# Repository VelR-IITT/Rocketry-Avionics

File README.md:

# Rocketry-Avionics 🚀

Welcome to the **Rocketry-Avionics** repository! This project is dedicated to the development of avionics systems for rocketry. It contains all the necessary files, code, and documentation to help you understand, build, and contribute to the project. 
---
## 📁 Repository Contents

This repository contains the following:

### 1. **Images** 📷
Contains visual assets, diagrams, and photos related to the project. These images are useful for understanding the design and assembly of components.

### 2. **Files for Components** 📄
Includes schematics, datasheets, and design files for various components used in the avionics system. These files are essential for replicating or modifying the project.

### 3. **Code** 💻
Contains the source code for the avionics system. This includes firmware, scripts, and any software required to operate the rocket's electronics.

### 4. **Instructions** 📝
Step-by-step guides and documentation to help you set up, assemble, and troubleshoot the avionics system.

---

## 📧 Contact

🌐 GitHub: [Pratham Chintamani](https://github.com/prathamchintamani) \
🌐 GitHub: [Pratik Raj](https://github.com/0823pratik)\
🌐 GitHub: [Bhavesh Jain](https://github.com/Bhavesh-Ja1n)\
🌐 GitHub: [Sravan Gantla](https://github.com/sravangantla007)

---

Happy building! 🚀✨

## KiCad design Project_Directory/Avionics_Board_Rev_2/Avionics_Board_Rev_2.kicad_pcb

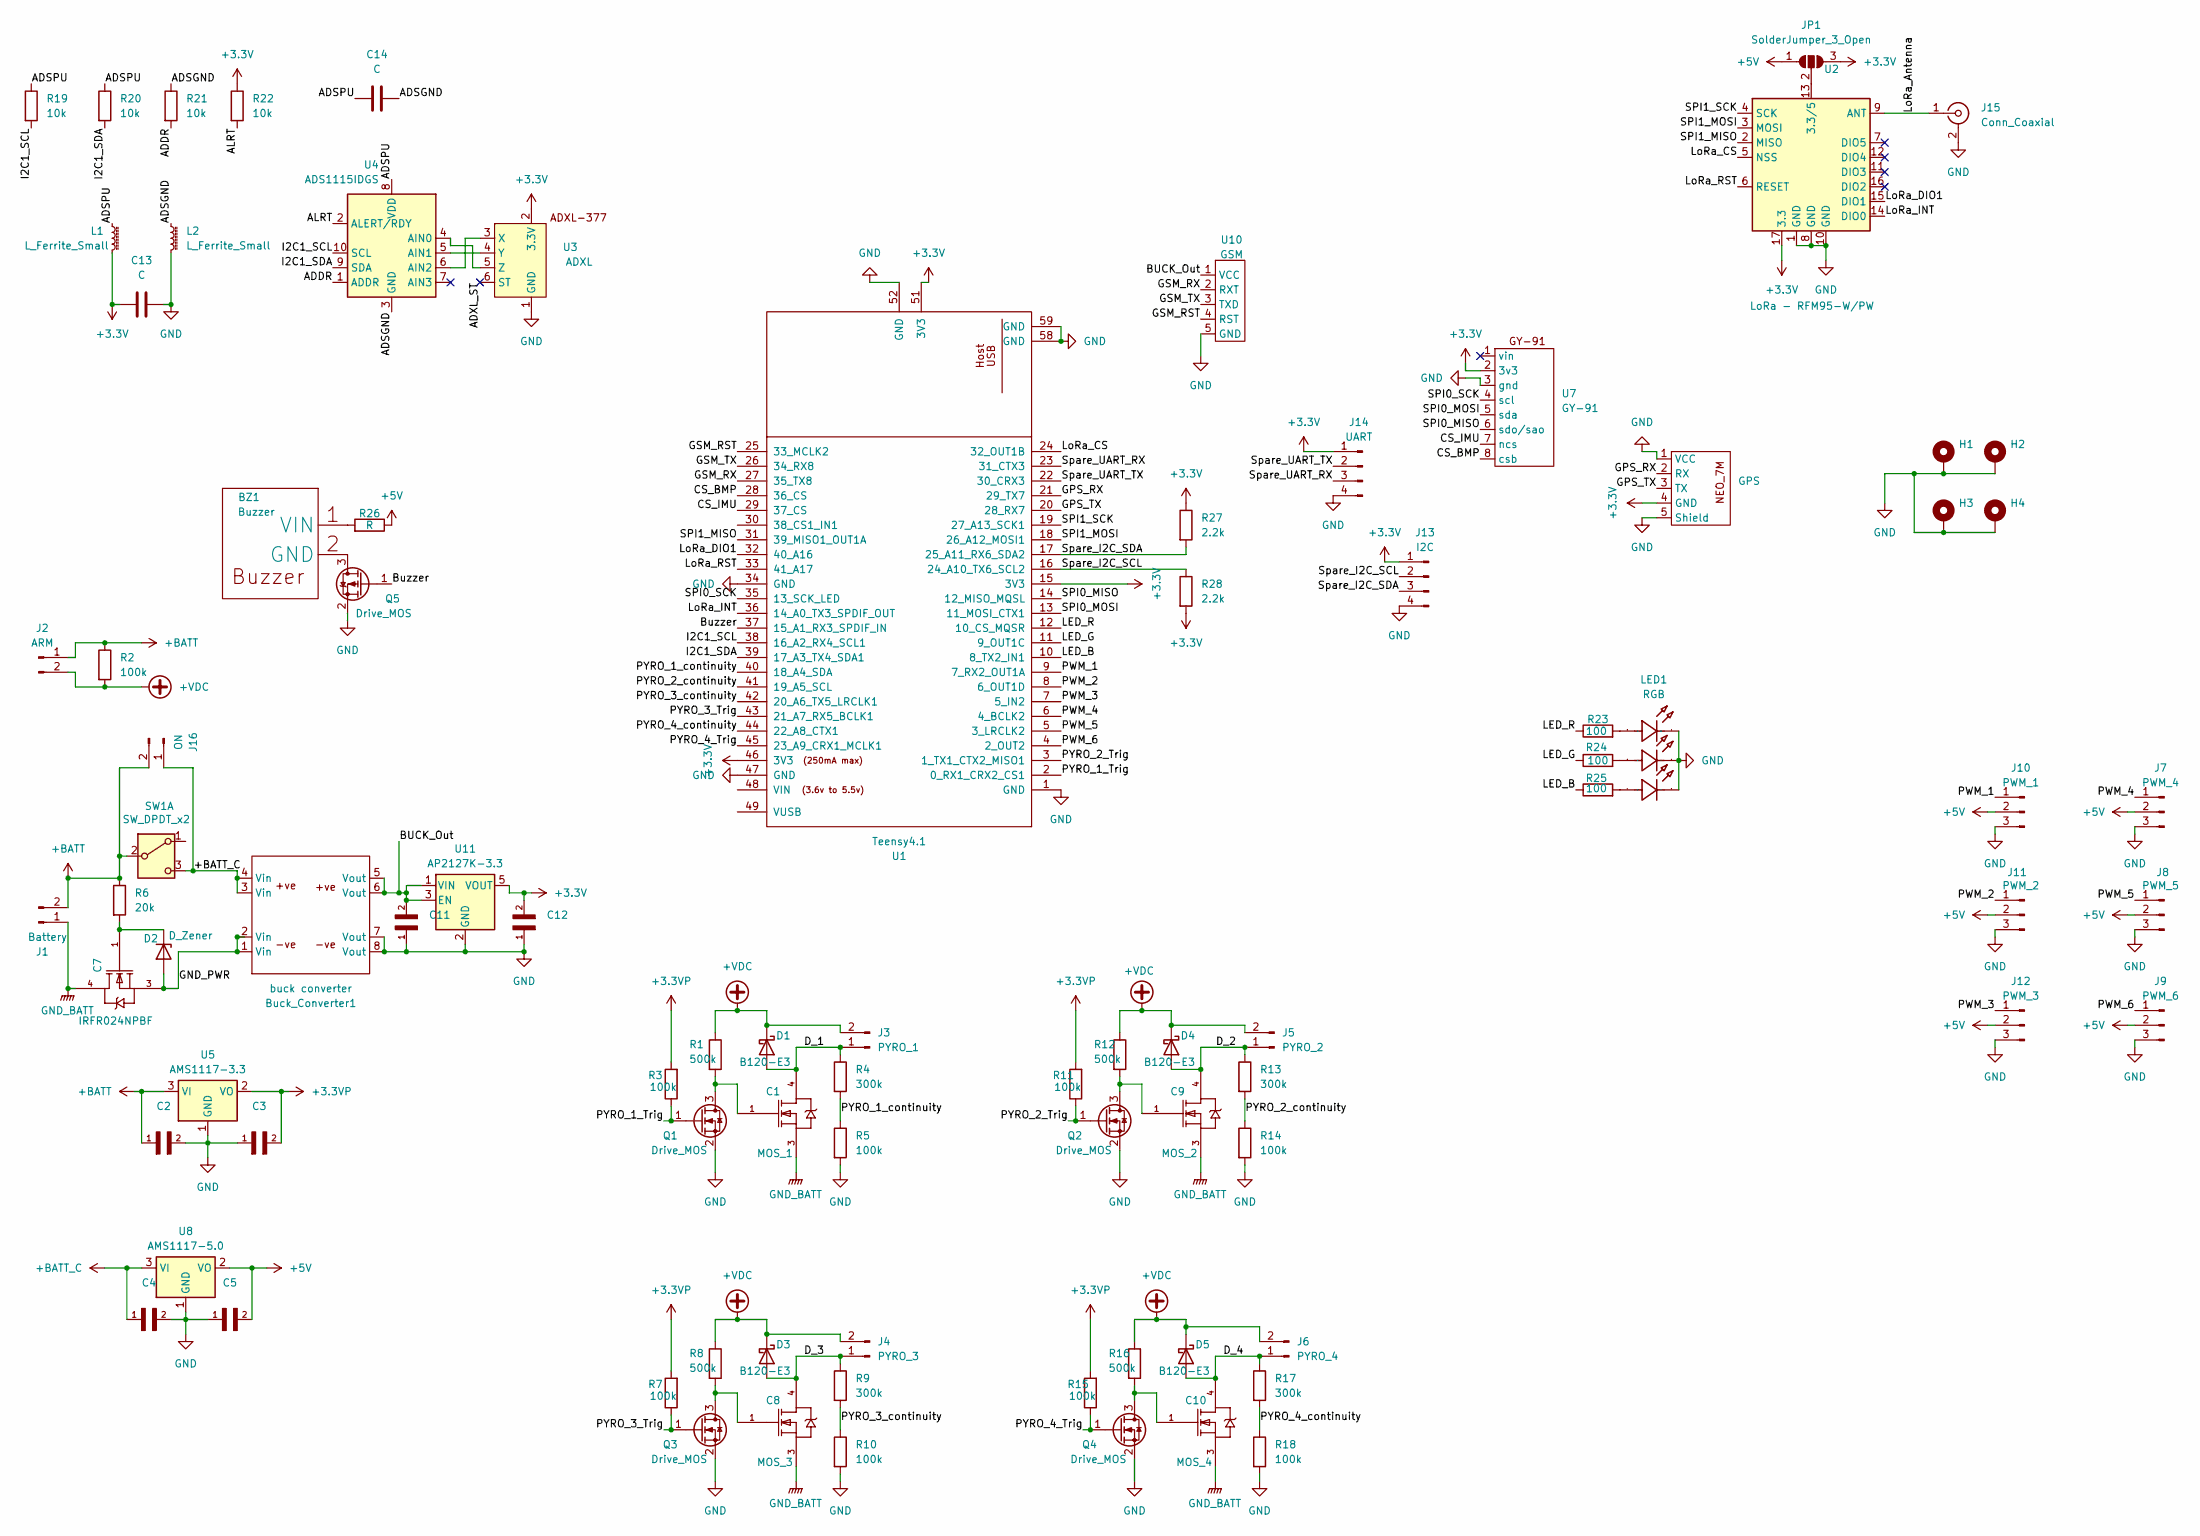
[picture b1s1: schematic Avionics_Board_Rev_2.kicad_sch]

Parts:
BZ1: Buzzer; Buzzer_TMB12A05
Buck_Converter1: buck converter; buck converter_corrected
C1: MOS_1; IRFR024NTRPBF-HXY Mosfet
C2, C3, C4, C5, C11, C12: C_0603_1608Metric_Pad1.08x0.95mm_HandSolder
C7: IRFR024NPBF; IRFR024NTRPBF-HXY Mosfet
C8: MOS_3; IRFR024NTRPBF-HXY Mosfet
C9: MOS_2; IRFR024NTRPBF-HXY Mosfet
C10: MOS_4; IRFR024NTRPBF-HXY Mosfet
C13: C; C_1206_3216Metric_Pad1.33x1.80mm_HandSolder
C14: C; C_1210_3225Metric_Pad1.33x2.70mm_HandSolder
D1, D3, D4, D5: B120-E3; D_SMA
D2: D_Zener; diode_
H1, H2, H3, H4: MountingHole_Pad; MountingHole_3.2mm_M3_DIN965_Pad_TopBottom
J1: Battery; AMASS_XT60PW-M_1x02_P7.20mm_Horizontal
J2: ARM; TerminalBlock_Phoenix_MKDS-1,5-2-5.08_1x02_P5.08mm_Horizont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
J3: PYRO_1; TerminalBlock_Phoenix_MKDS-1,5-2_1x02_P5.00mm_Horizontal
J4: PYRO_3; TerminalBlock_Phoenix_MKDS-1,5-2_1x02_P5.00mm_Horizontal
J5: PYRO_2; TerminalBlock_Phoenix_MKDS-1,5-2_1x02_P5.00mm_Horizontal
J6: PYRO_4; TerminalBlock_Phoenix_MKDS-1,5-2_1x02_P5.00mm_Horizontal
J7: PWM_4; PinHeader_1x03_P2.54mm_Vertical
J8: PWM_5; PinHeader_1x03_P2.54mm_Vertical
J9: PWM_6; PinHeader_1x03_P2.54mm_Vertical
J10: PWM_1; PinHeader_1x03_P2.54mm_Vertical
J11: PWM_2; PinHeader_1x03_P2.54mm_Vertical
J12: PWM_3; PinHeader_1x03_P2.54mm_Vertical
J13: I2C; JST_EH_B4B-EH-A_1x04_P2.50mm_Vertical
J14: UART; JST_EH_B4B-EH-A_1x04_P2.50mm_Vertical
J15: Conn_Coaxial; SMA_Samtec_SMA-J-P-H-ST-EM1_EdgeMount
J16: ON; TerminalBlock_Phoenix_MKDS-1,5-2-5.08_1x02_P5.08mm_Horizont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
JP1: SolderJumper_3_Open; SolderJumper-3_P2.0mm_Open_TrianglePad1.0x1.5mm
L1, L2: L_Ferrite_Small; L_1206_3216Metric_Pad1.22x1.90mm_HandSolder
LED1: RGB; XL-z3535rgbasg_RGB_LED; Manufacturer Part XL-Z3535RGBA-SG
Q1, Q2, Q3, Q4, Q5: Drive_MOS; SOT-23
R1, R8, R12, R16: 500k; R_1206_3216Metric_Pad1.30x1.75mm_HandSolder
R2, R3, R5, R7, R10, R11, R14, R15, R18: 100k; R_1206_3216Metric_Pad1.30x1.75mm_HandSolder
R4, R9, R13, R17: 300k; R_1206_3216Metric_Pad1.30x1.75mm_HandSolder
R6: 20k; R_1206_3216Metric_Pad1.30x1.75mm_HandSolder
R19, R20, R21, R22: 10k; C_1206_3216Metric_Pad1.33x1.80mm_HandSolder
R23, R24, R25: 100; R_1206_3216Metric_Pad1.30x1.75mm_HandSolder
R26: R; R_1206_3216Metric_Pad1.30x1.75mm_HandSolder
R27, R28: 2.2k; R_1206_3216Metric_Pad1.30x1.75mm_HandSolder
SW1: SW_DPDT_x2; Switch exp
U1: Teensy4.1; Teensy_4.1
U2: LoRa - RFM95-W/PW; RFM95W,PW
U3: ADXL; ADXL377_SparkFun_Module
U4: ADS1115IDGS; TSSOP-10_3x3mm_P0.5mm
U5: AMS1117-3.3; SOT-223-3_TabPin2
U6: GPS; JST-SH 1mm 4 Pin Male E Type Vertical Single Row WTB Connec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
U7: GY-91; gy91
U8: AMS1117-5.0; SOT-223-3_TabPin2
U10: GSM; JST_EH_B5B-EH-A_1x05_P2.50mm_Vertical
U11: AP2127K-3.3; SOT-23-5

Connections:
+3.3V: C12.2, C13.1, J13.1, J14.1, JP1.3 (B), L1.2, R22.1, R27.1, R28.2, U1.15 (3V3), U1.46 (3V3), U1.51 (3V3), U2.17 (3.3), U3.2 (3.3V), U6.4 (GND), U7.2 (3v3), U11.5 (VOUT)
+3.3VP: C3.2, R3.2, R7.2, R11.2, R15.2, U5.2 (VO)
+5V: C5.2, J7.2, J8.2, J9.2, J10.2, J11.2, J12.2, JP1.1 (A), R26.1, U8.2 (VO)
+BATT: C2.1, J1.2, J2.1, J16.2, R2.1, R6.1, SW1.2 (B), U5.3 (VI)
+BATT_C: Buck_Converter1.3 (Vin), Buck_Converter1.4 (Vin), C4.1, J16.1, SW1.3 (C), U8.3 (VI)
+VDC: D1.1 (K), D3.1 (K), D4.1 (K), D5.1 (K), J2.2, J3.2, J4.2, J5.2, J6.2, R1.1, R2.2, R8.1, R12.1, R16.1
/ADDR: R21.2, U4.1 (ADDR)
/ADSGND: C14.2, L2.1, R21.1, U4.3 (GND)
/ADSPU: C14.1, L1.1, R19.1, R20.1, U4.8 (VDD)
/ADXL_ST: U3.6 (ST)
/ALRT: R22.2, U4.2 (ALERT/RDY)
/BUCK_Out: Buck_Converter1.5 (Vout), Buck_Converter1.6 (Vout), C11.2, U10.1 (VCC), U11.1 (VIN), U11.3 (EN)
/Buzzer: Q5.1 (G), U1.37 (15_A1_RX3_SPDIF_IN)
/CS_BMP: U1.28 (36_CS), U7.8 (csb)
/CS_IMU: U1.29 (37_CS), U7.7 (ncs)
/D_1: C1.4, D1.2 (A), J3.1, R4.1
/D_2: C9.4, D4.2 (A), J5.1, R13.1
/D_3: C8.4, D3.2 (A), J4.1, R9.1
/D_4: C10.4, D5.2 (A), J6.1, R17.1
/GND_PWR: Buck_Converter1.1 (Vin), Buck_Converter1.2 (Vin), C7.3, D2.2 (A)
/GPS_RX: U1.21 (29_TX7), U6.2 (RX)
/GPS_TX: U1.20 (28_RX7), U6.3 (TX)
/GSM_RST: U1.25 (33_MCLK2), U10.4 (RST)
/GSM_RX: U1.27 (35_TX8), U10.2 (RXT)
/GSM_TX: U1.26 (34_RX8), U10.3 (TXD)
/I2C1_SCL: R19.2, U1.38 (16_A2_RX4_SCL1), U4.10 (SCL)
/I2C1_SDA: R20.2, U1.39 (17_A3_TX4_SDA1), U4.9 (SDA)
/LED_B: R25.1, U1.10 (8_TX2_IN1)
/LED_G: R24.1, U1.11 (9_OUT1C)
/LED_R: R23.1, U1.12 (10_CS_MQSR)
/LoRa_Antenna: J15.1 (In), U2.9 (ANT)
/LoRa_CS: U1.24 (32_OUT1B), U2.5 (NSS)
/LoRa_DIO1: U1.32 (40_A16), U2.15 (DIO1)
/LoRa_INT: U1.36 (14_A0_TX3_SPDIF_OUT), U2.14 (DIO0)
/LoRa_RST: U1.33 (41_A17), U2.6 (RESET)
/PWM_1: J10.1, U1.9 (7_RX2_OUT1A)
/PWM_2: J11.1, U1.8 (6_OUT1D)
/PWM_3: J12.1, U1.7 (5_IN2)
/PWM_4: J7.1, U1.6 (4_BCLK2)
/PWM_5: J8.1, U1.5 (3_LRCLK2)
/PWM_6: J9.1, U1.4 (2_OUT2)
/PYRO_1_Trig: Q1.1 (G), R3.1, U1.2 (0_RX1_CRX2_CS1)
/PYRO_1_continuity: R4.2, R5.1, U1.40 (18_A4_SDA)
/PYRO_2_Trig: Q2.1 (G), R11.1, U1.3 (1_TX1_CTX2_MISO1)
/PYRO_2_continuity: R13.2, R14.1, U1.41 (19_A5_SCL)
/PYRO_3_Trig: Q3.1 (G), R7.1, U1.43 (21_A7_RX5_BCLK1)
/PYRO_3_continuity: R9.2, R10.1, U1.42 (20_A6_TX5_LRCLK1)
/PYRO_4_Trig: Q4.1 (G), R15.1, U1.45 (23_A9_CRX1_MCLK1)
/PYRO_4_continuity: R17.2, R18.1, U1.44 (22_A8_CTX1)
/SPI0_MISO: U1.14 (12_MISO_MQSL), U7.6 (sdo/sao)
/SPI0_MOSI: U1.13 (11_MOSI_CTX1), U7.5 (sda)
/SPI0_SCK: U1.35 (13_SCK_LED), U7.4 (scl)
/SPI1_MISO: U1.31 (39_MISO1_OUT1A), U2.2 (MISO)
/SPI1_MOSI: U1.18 (26_A12_MOSI1), U2.3 (MOSI)
/SPI1_SCK: U1.19 (27_A13_SCK1), U2.4 (SCK)
/Spare_I2C_SCL: J13.2, R28.1, U1.16 (24_A10_TX6_SCL2)
/Spare_I2C_SDA: J13.3, R27.2, U1.17 (25_A11_RX6_SDA2)
/Spare_UART_RX: J14.3, U1.23 (31_CTX3)
/Spare_UART_TX: J14.2, U1.22 (30_CRX3)
GND: Buck_Converter1.7 (Vout), Buck_Converter1.8 (Vout), C2.2, C3.1, C4.2, C5.1, C11.1, C12.1, C13.2, H1.1, H2.1, H3.1, H4.1, J7.3, J8.3, J9.3, J10.3, J11.3, J12.3, J13.4, J14.4, J15.2 (Ext), L2.2, LED1.1 (-), LED1.2 (-), LED1.3 (1), Q1.2 (S), Q2.2 (S), Q3.2 (S), Q4.2 (S), Q5.2 (S), R5.2, R10.2, R14.2, R18.2, U1.1 (GND), U1.34 (GND), U1.47 (GND), U1.52 (GND), U1.58 (GND), U1.59 (GND), U2.1 (GND), U2.8 (GND), U2.10 (GND), U3.1 (GND), U5.1 (GND), U6.1 (VCC), U6.5 (Shield), U7.3 (gnd), U8.1 (GND), U10.5 (GND), U11.2 (GND)
GND_BATT: C1.3, C7.4, C8.3, C9.3, C10.3, J1.1
unnamed: BZ1.2 (GND), Q5.3 (D)
unnamed: BZ1.1 (VIN), R26.2
unnamed: C7.1, D2.1 (K), R6.2
unnamed: JP1.2 (C), U2.13 (3.3/5)
unnamed: LED1.4 (+), R23.2
unnamed: LED1.5 (+), R24.2
unnamed: LED1.6 (+), R25.2
unnamed: C1.1, Q1.3 (D), R1.2
unnamed: C9.1, Q2.3 (D), R12.2
unnamed: C8.1, Q3.3 (D), R8.2
unnamed: C10.1, Q4.3 (D), R16.2
unnamed: U3.3 (X), U4.6 (AIN2)
unnamed: U3.4 (Y), U4.5 (AIN1)
unnamed: U3.5 (Z), U4.4 (AIN0)

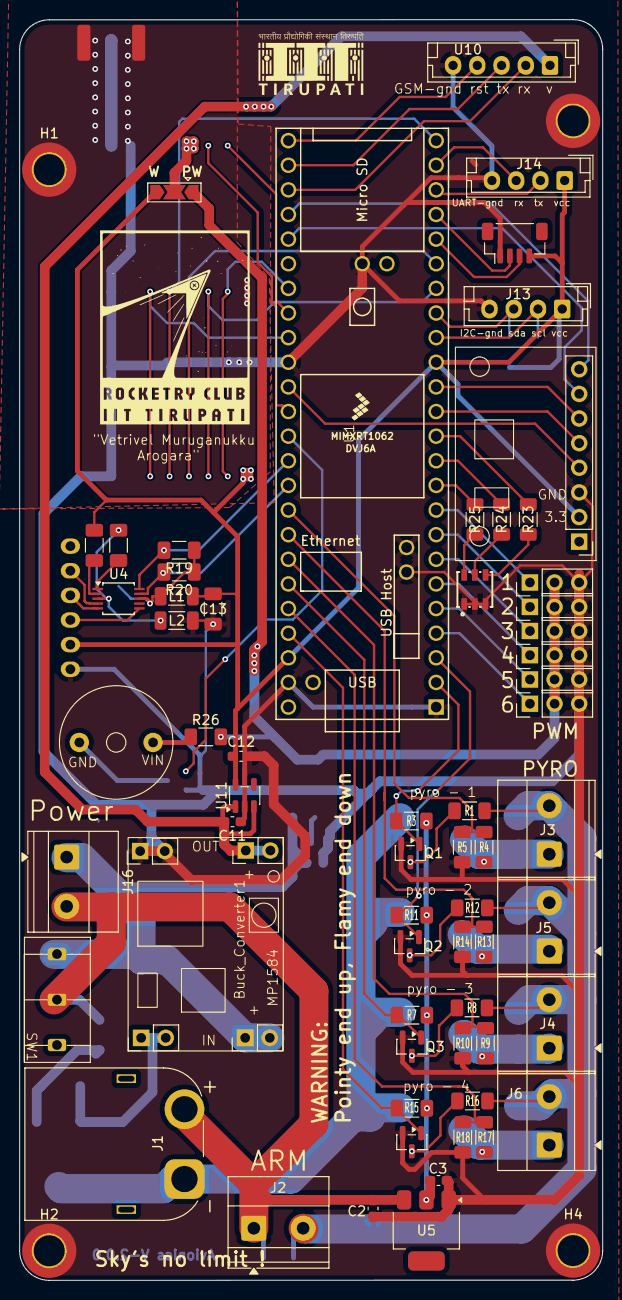
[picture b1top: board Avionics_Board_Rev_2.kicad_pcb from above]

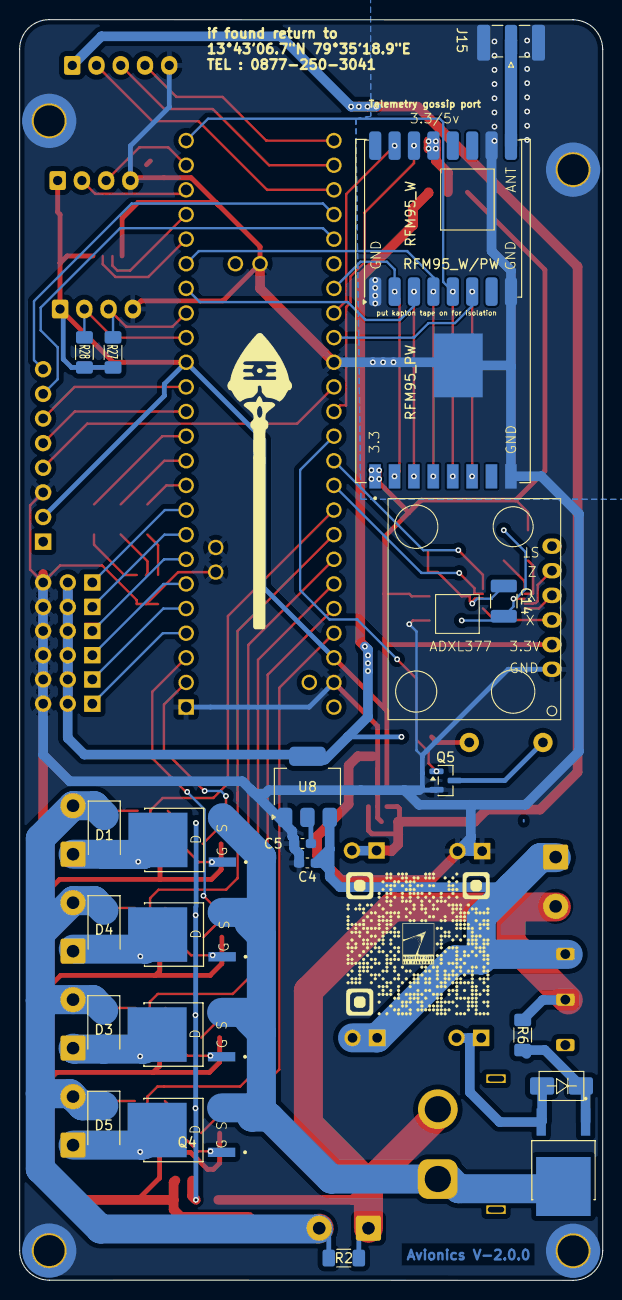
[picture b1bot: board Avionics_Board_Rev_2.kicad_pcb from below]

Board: 2 copper layers, 60.1 x 130.0 mm, 88 parts (22 on the bottom side), 74 nets.

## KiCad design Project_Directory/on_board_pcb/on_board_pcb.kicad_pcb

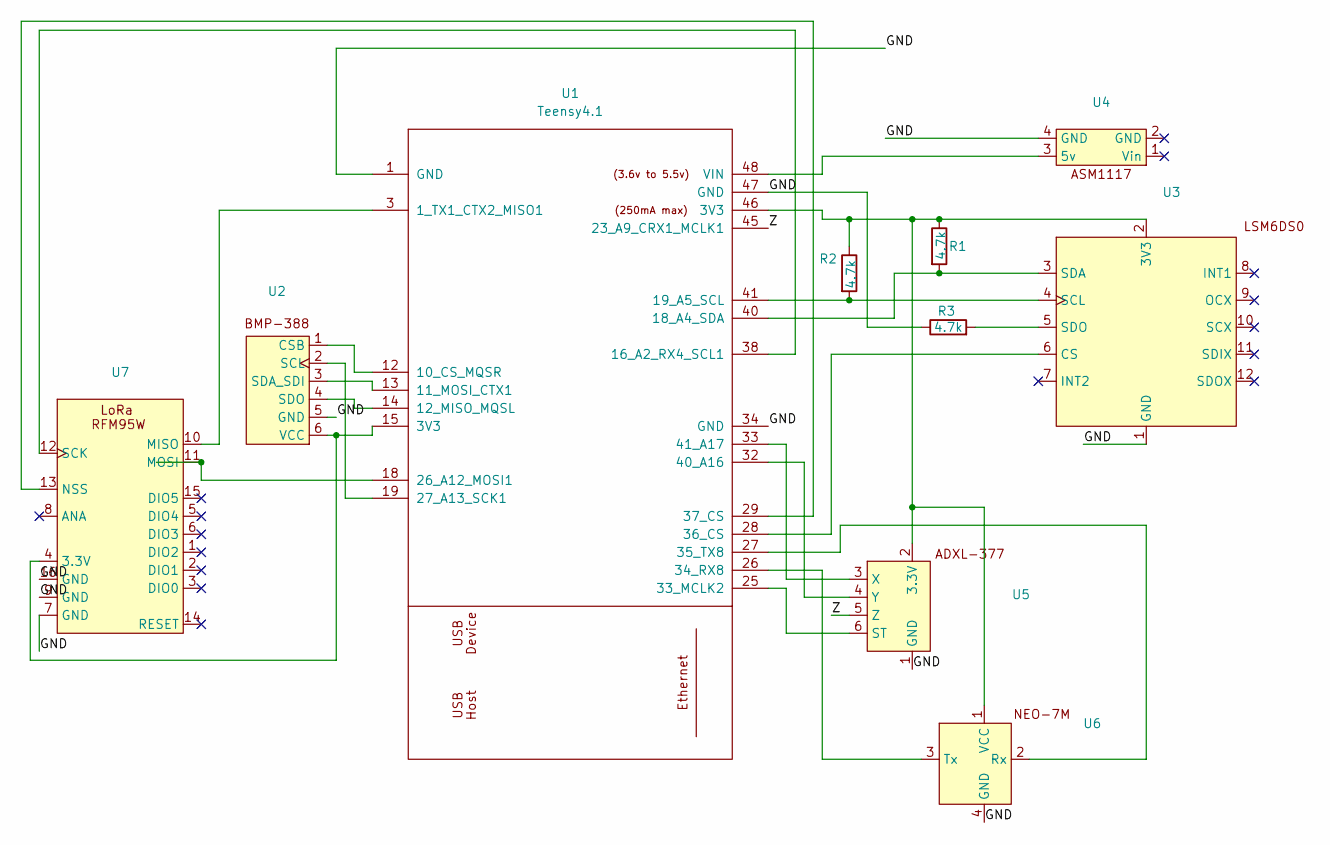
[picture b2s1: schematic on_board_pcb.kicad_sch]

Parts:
R1, R2, R3: 4.7k; R_Axial_DIN0207_L6.3mm_D2.5mm_P7.62mm_Horizontal
U1: Teensy4.1; Teensy-4.1
U2: BMP388
U3: LSM6DS0
U4: AMS1117
U5: ADXL377
U6: NEO_7M
U7: RFM95W

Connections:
/GND: R3.1, U1.1 (GND), U1.34 (GND), U1.47 (GND), U2.5 (GND), U3.1 (GND), U4.4 (GND), U5.1 (GND), U6.4 (GND), U7.7 (GND), U7.9 (GND), U7.16 (GND)
/Z: U1.45 (23_A9_CRX1_MCLK1), U5.5 (Z)
unnamed: U1.3 (1_TX1_CTX2_MISO1), U7.10 (MISO)
unnamed: U1.12 (10_CS_MQSR), U2.1 (CSB)
unnamed: U1.13 (11_MOSI_CTX1), U2.3 (SDA_SDI)
unnamed: U1.14 (12_MISO_MQSL), U2.4 (SDO)
unnamed: U1.38 (16_A2_RX4_SCL1), U7.12 (SCK)
unnamed: R1.2, U1.40 (18_A4_SDA), U3.3 (SDA)
unnamed: R2.2, U1.41 (19_A5_SCL), U3.4 (SCL)
unnamed: U1.18 (26_A12_MOSI1), U7.11 (MOSI)
unnamed: U1.19 (27_A13_SCK1), U2.2 (SCL)
unnamed: U1.25 (33_MCLK2), U5.6 (ST)
unnamed: U1.26 (34_RX8), U6.3 (Tx)
unnamed: U1.27 (35_TX8), U6.2 (Rx)
unnamed: U1.28 (36_CS), U3.6 (CS)
unnamed: U1.29 (37_CS), U7.13 (NSS)
unnamed: U1.32 (40_A16), U5.4 (Y)
unnamed: U1.33 (41_A17), U5.3 (X)
unnamed: U1.48 (VIN), U4.3 (5v)
unnamed: U1.15 (3V3), U2.6 (VCC), U7.4 (3.3V)
unnamed: R1.1, R2.1, U1.46 (3V3), U3.2 (3V3), U5.2 (3.3V), U6.1 (VCC)
unnamed: R3.2, U3.5 (SDO)

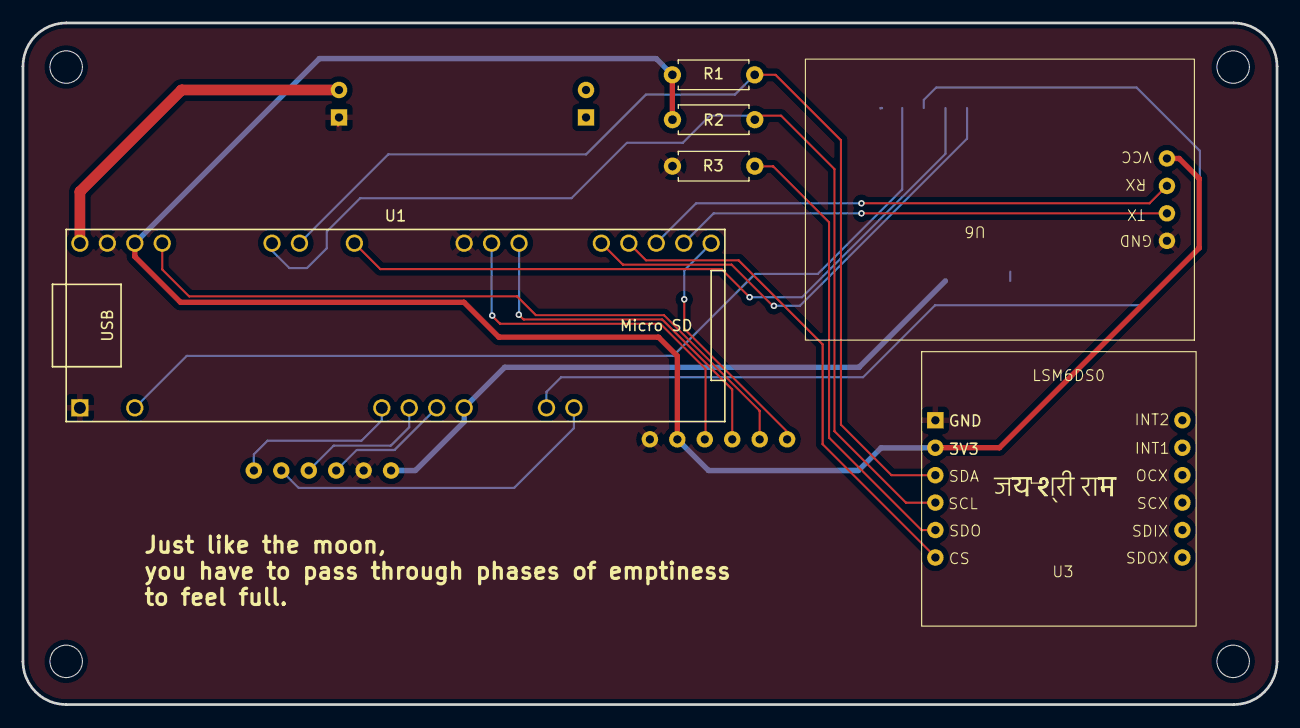
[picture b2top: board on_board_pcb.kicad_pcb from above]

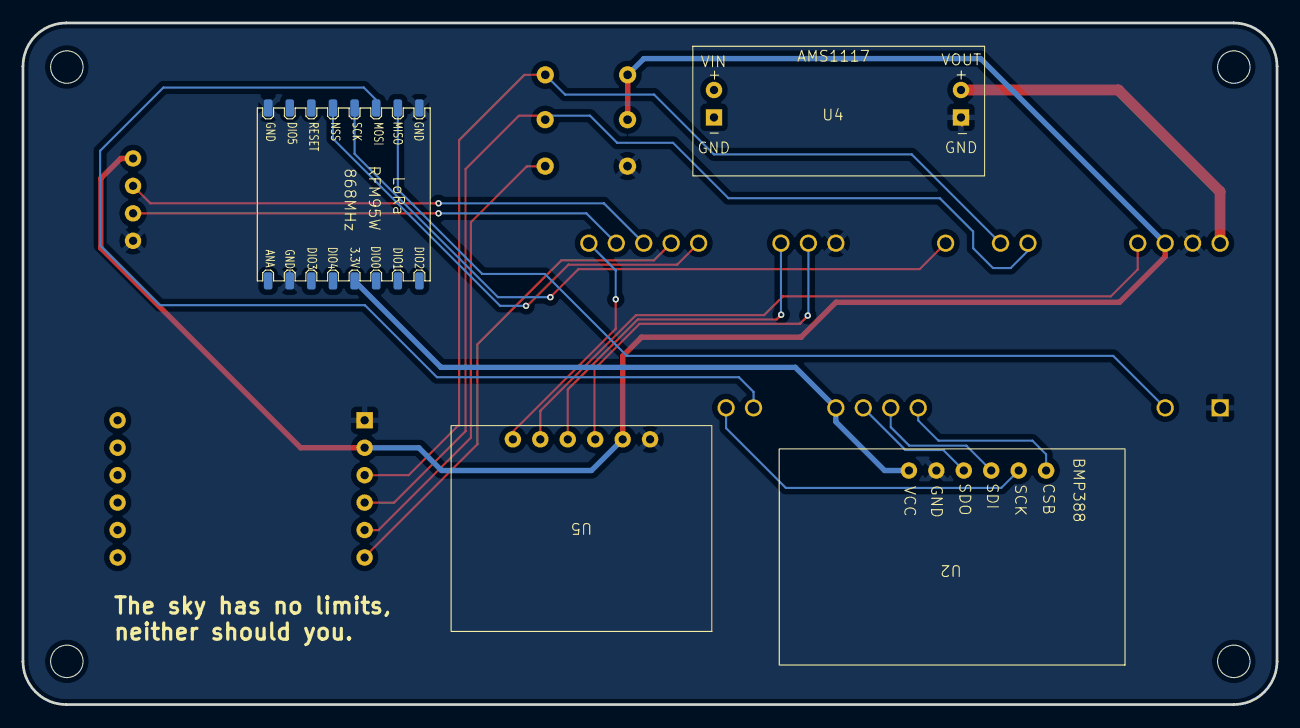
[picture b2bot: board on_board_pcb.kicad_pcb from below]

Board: 2 copper layers, 116.1 x 63.1 mm, 10 parts (4 on the bottom side), 22 nets.

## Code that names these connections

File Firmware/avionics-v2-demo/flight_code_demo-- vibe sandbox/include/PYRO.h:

#include <Arduino.h>

#include<FreeRTOS.h>
#include <task.h>

#define PYRO_1_TRIG 0
#define PYRO_2_TRIG 1
#define PYRO_3_TRIG 21
#define PYRO_4_TRIG 23

#define PYRO_1_CONT 18
#define PYRO_2_CONT 19
#define PYRO_3_CONT 20
#define PYRO_4_CONT 22

#define CONTIN_THRESHOLD 8/3 - 1



int pyro_continuity[4] = {PYRO_1_CONT, PYRO_2_CONT, PYRO_3_CONT, PYRO_4_CONT};
int Pyro_Trigger[4] = {PYRO_1_TRIG, PYRO_2_TRIG, PYRO_3_TRIG, PYRO_4_TRIG};

uint8_t Pyro_Contin = 0x00; // 0b00001111 continuity

bool good_continuity = false;

#define IGNITION_DURATION 1000

enum pyro_mode_t
{
    PYRO_1      =   1,  // 0b00000001
    PYRO_2      =   2,  // 0b00000010
    PYRO_3      =   4,  // 0b00000100
    PYRO_4      =   8,  // 0b00001000
    PYRO_12     =   3,  // 0b00000011
    PYRO_34     =   12, // 0b00001100
    PYRO_12_34  =   15  // 0b00001111
};

pyro_mode_t Pyro_Con_Mode = PYRO_1;
pyro_mode_t Pyro_Mode     = PYRO_1;


void Pyro_Continuity_Task(void *pvParameters)
{
    for(int i = 0; i < 4; i++)
    {
        pinMode(Pyro_Trigger[i], OUTPUT);
        digitalWrite(Pyro_Trigger[i], HIGH);
    }
    for(int i = 0; i < 4; i++)
    {
        pinMode(pyro_continuity[i], INPUT);
    }
    
    TickType_t lastWake = xTaskGetTickCount();

    while(1)
    {
        for(int i = 0; i < 4; i++)
        {
            if(analogRead(pyro_continuity[i]) >= CONTIN_THRESHOLD)
            {
                Pyro_Contin |= (1 << i);
            }
            else
            {
                Pyro_Contin &= ~(1 << i);
            }
        }

      if((uint8_t)Pyro_Contin == (uint8_t)Pyro_Con_Mode)
        good_continuity = true;
      else
        good_continuity = false;

        vTaskDelayUntil(&lastWake, pdMS_TO_TICKS(500));
        
    }

}

void Pyro_Trigger_Task(void *pvParameters)
{
    

    for(int i = 0; i < 4; i++)
        digitalWrite(Pyro_Trigger[i], !(Pyro_Mode & (1 << i)));

    vTaskDelay(pdMS_TO_TICKS(IGNITION_DURATION));

    for(int i = 0; i < 4; i++)
        digitalWrite(Pyro_Trigger[i], HIGH);
}

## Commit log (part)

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2025-01-29 adding the project files
2025-01-29 added the symbols and footprints in an organized way
2025-01-29 added the instructions
2025-01-29 updated instructions
2025-01-31 minor changes
2025-02-06 added lora footprint
2025-02-06 completed LoRa RFM95W Footprint
2025-02-07 added symbol and footprint for arduino nano
2025-02-07 95% of adxl377 footprint added and fixed an error in adxl377 symbol
2025-02-07 added some images
2025-02-08 added AMS1117 footprint
2025-02-08 added LoRa symbol. unstable version-need to fix LSMD6S0 symbol
2025-02-08 fixed LSMD6S0 symbol and footprint
2025-02-17 fixed bmp388
2025-02-18 finished schematic
2025-02-18 added some images and schematic pdf
2025-02-18 made pcb
2025-04-02 preliminary pcb routing
2025-04-12 p1 board semifinal
2025-04-12 added updated schematic. minor cosmetic changes
2025-08-05 arduino sketches and some images
2026-02-14 added rev-2 board
2026-02-14 started working.
2026-02-17 temp
2026-02-21 schematic
2026-02-21 working
2026-02-21 in progess
2026-02-21 progress on schematic and pcb
2026-02-21 more work
2026-02-22 modified gsm to be a jst connector
2026-02-22 removed colon in file name
2026-02-22 changes to schematic
2026-02-27 save
2026-02-27 schematic changes
2026-03-01 schematic and pcb commit -1
2026-03-04 resistor values added
2026-03-04 values changed 4/3/26
2026-03-05 switch added 1
2026-03-05 switch update 2
2026-03-06 Modification 1 on 5 march
2026-03-06 Modification 2 5 march
2026-03-06 updated foot prints
2026-03-06 corrected buckconverter and drive mos
2026-03-06 patch work 5 march
2026-03-07 modification 1 7 mmarch
2026-03-07 Modification 2 march 7
2026-03-07 Modification 3 7th march
2026-03-07 QR added
2026-03-07 asthetics
2026-03-08 final additions , v-2.0.0
2026-03-08 gerber files
2026-04-06 project setup
2026-04-08 feat: add GSM state enum and ring buffer structure
    Current Changes
    - introduced the architecture by objectifying the events during the operation of SMS send/recieve
    - introduced gsm_state_t for future FSM implementation
    - added ring buffer structure for UART data handling
    - no integration with UART or parser yet
    - need to look over the gsm_state_t on whether could be transferred to the GSM.h file instead over here
2026-04-08 added hardware.h references
2026-04-09 started making myLoRa
2026-04-11 Binded hardware.h and Lora.h
    added reading mode enum; increased accuracy of frequency;
2026-04-17 added an interrupt function
2026-05-18 implemented free rtos
